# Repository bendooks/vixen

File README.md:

Reverse engineering a VIC-20 RAM expansion
==========================================

This is a project to reverse engineer a Commodore VIC-20 memory expansion
from the old 8-bit computer days. This repository has several versions of
the board, a talk describing the process and related documentation.

The [talk](./talk/) directory contains all the relevant presentation files
and the [pcb](./pcb) directory has various PCB design projects (currently
mostly in Eagle 7).

There are some [pictures](https://photos.app.goo.gl/yPw7znJ7fA79bZMN6) of
both the original boards and my rebuilds.

Links
-----

- FOSDEM 2020 [talk](https://archive.fosdem.org/2020/schedule/event/retro_reverse_engineering_vic_20_cartridge/)
- Computing history [page](http://www.computinghistory.org.uk/det/32521/Vixen-Switchable-16K-RAM/)
- Retro-computing [page](https://www.retrocomputers.online/product/vixen-switchable-16k-ram/) includes [manual](https://www.retrocomputers.online/wp-content/uploads/2020/11/Vixen16kRAM.pdf)
- Commodore info [page](https://www.commodore-info.com/cartridge/item/vixen_16k/en/desktop)
- Nightfall crea [page](https://www.nightfallcrew.com/18/05/2010/vixen-switchable-16k-ram-for-commodore-vic-20/) includes detailed pictures.

License
-------

All work is under CC-BY-SA v4 unless otherwise stated.

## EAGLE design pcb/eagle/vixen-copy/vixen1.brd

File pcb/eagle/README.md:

Eagle PCB files
===============

These are the PCB file projects for the re-build of the original [vixen-copy](./vixen-copy/) and a new variant which is modified to support 64KiB-ish memory expansion [vixen-copy-64k](./vixen-copy-64ki)

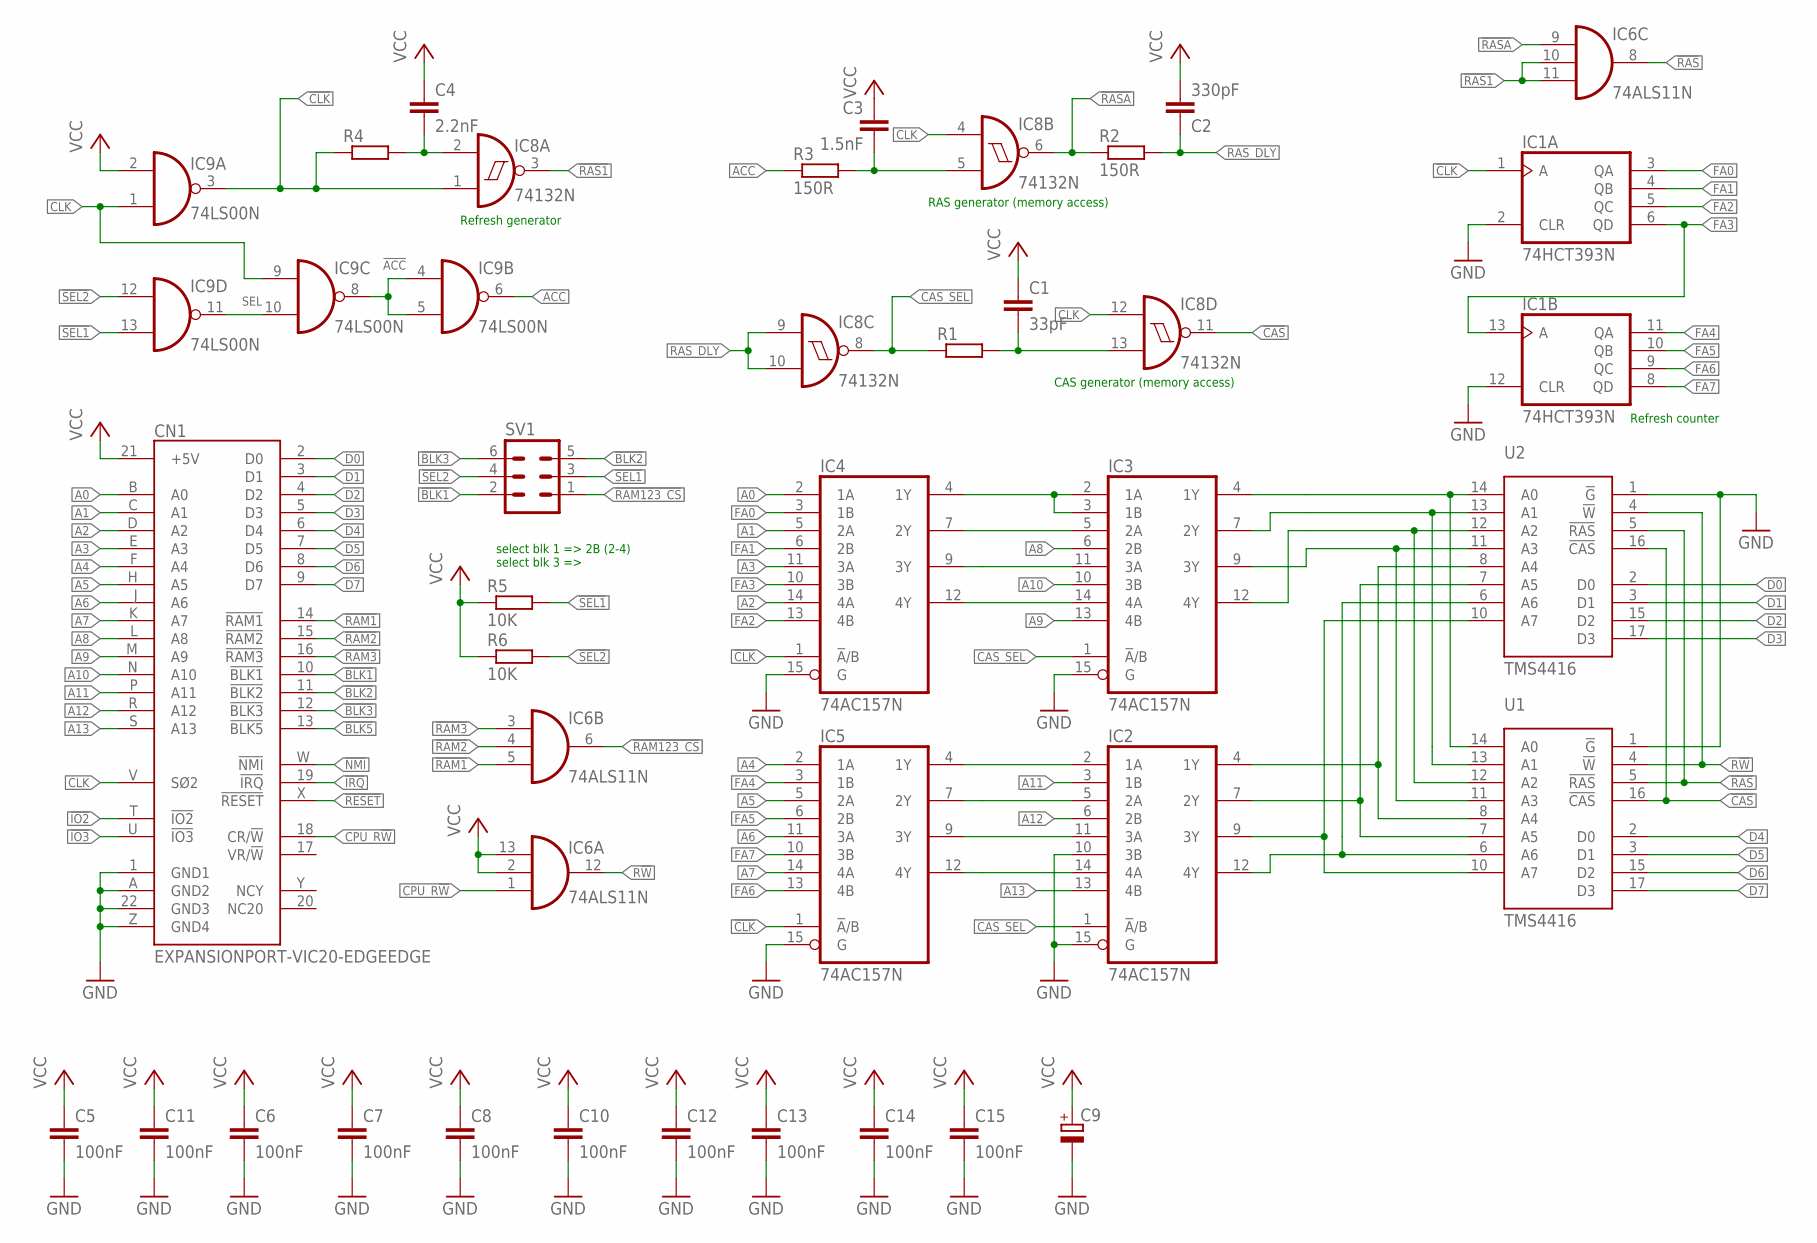
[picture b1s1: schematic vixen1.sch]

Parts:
C1: 33pF; C025-025X050
C2: 330pF; C025-025X050
C3: 1.5nF; C025-025X050
C4: 2.2nF; C025-025X050
C5, C6, C7, C8, C10, C11, C12, C13, C14, C15: 100nF; C025-025X050
C9: CPOL-EUE15-5AXIAL; E15-5
CN1: EXPANSIONPORT-VIC20-EDGEEDGE; UPS44EDGE
IC1: 74HCT393N; DIL14
IC2, IC3, IC4, IC5: 74AC157N; DIL16
IC6: 74ALS11N; DIL14
IC8: 74132N; DIL14
IC9: 74LS00N; DIL14
R1, R4: R-EU_0204/7; 0204/7
R2, R3: 150R; 0204/7
R5, R6: 10K; 0204/7
SV1: MA03-2
U1, U2: TMS4416; DIL18

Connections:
!ACC: IC9.4 (I0), IC9.5 (I1), IC9.8 (O)
!BLK1: CN1.10 (!BLK1), SV1.2
!BLK2: CN1.11 (!BLK2), SV1.5
!BLK3: CN1.12 (!BLK3), SV1.6
!BLK5: CN1.13 (!BLK5)
!CAS: IC8.11 (O), U1.16 (!CAS), U2.16 (!CAS)
!CLK: IC1.1 (A), IC4.1 (!A!/B), IC5.1 (!A!/B), IC8.1 (I0), IC9.3 (O), R4.1
!IO2: CN1.T (!IO2)
!IO3: CN1.U (!IO3)
!IRQ: CN1.19 (!IRQ)
!NMI: CN1.W (!NMI)
!RAM1: CN1.14 (!RAM1), IC6.5 (I2)
!RAM2: CN1.15 (!RAM2), IC6.4 (I1)
!RAM3: CN1.16 (!RAM3), IC6.3 (I0)
!RAM123_CS: IC6.6 (O), SV1.1
!RAS: IC6.8 (O), U1.5 (!RAS), U2.5 (!RAS)
!RAS1: IC6.10 (I1), IC6.11 (I2), IC8.3 (O)
!RASA: IC6.9 (I0), IC8.6 (O), R2.1
!RESET: CN1.X (!RESET)
!SEL1: IC9.13 (I1), R5.2, SV1.3
!SEL2: IC9.12 (I0), R6.2, SV1.4
A0: CN1.B (A0), IC4.2 (1A)
A1: CN1.C (A1), IC4.5 (2A)
A2: CN1.D (A2), IC4.14 (4A)
A3: CN1.E (A3), IC4.11 (3A)
A4: CN1.F (A4), IC5.2 (1A)
A5: CN1.H (A5), IC5.5 (2A)
A6: CN1.J (A6), IC5.11 (3A)
A7: CN1.K (A7), IC5.14 (4A)
A8: CN1.L (A8), IC3.6 (2B)
A9: CN1.M (A9), IC3.13 (4B)
A10: CN1.N (A10), IC3.10 (3B)
A11: CN1.P (A11), IC2.3 (1B)
A12: CN1.R (A12), IC2.6 (2B)
A13: CN1.S (A13), IC2.13 (4B)
ACC: IC9.6 (O), R3.1
CAS_RC: C1.2, IC8.13 (I1), R1.2
CAS_RC1: C4.2, IC8.2 (I1), R4.2
CAS_SEL: IC2.1 (!A!/B), IC3.1 (!A!/B), IC8.8 (O), R1.1
CLK: CN1.V (SØ2), IC8.4 (I0), IC8.12 (I0), IC9.1 (I0), IC9.9 (I0)
CPU_R!W: CN1.18 (CR/!W), IC6.1 (I0)
D0: CN1.2 (D0), U2.2 (D0)
D1: CN1.3 (D1), U2.3 (D1)
D2: CN1.4 (D2), U2.15 (D2)
D3: CN1.5 (D3), U2.17 (D3)
D4: CN1.6 (D4), U1.2 (D0)
D5: CN1.7 (D5), U1.3 (D1)
D6: CN1.8 (D6), U1.15 (D2)
D7: CN1.9 (D7), U1.17 (D3)
FA0: IC1.3 (QA), IC4.3 (1B)
FA1: IC1.4 (QB), IC4.6 (2B)
FA2: IC1.5 (QC), IC4.13 (4B)
FA3: IC1.6 (QD), IC1.13 (A), IC4.10 (3B)
FA4: IC1.11 (QA), IC5.3 (1B)
FA5: IC1.10 (QB), IC5.6 (2B)
FA6: IC1.9 (QC), IC5.13 (4B)
FA7: IC1.8 (QD), IC5.10 (3B)
GND: C5.2, C6.2, C7.2, C8.2, C9.-, C10.2, C11.2, C12.2, C13.2, C14.2, C15.2, CN1.1 (GND1), CN1.22 (GND3), CN1.A (GND2), CN1.Z (GND4), IC1.2 (CLR), IC1.7 (GND), IC1.12 (CLR), IC2.8 (GND), IC2.10 (3B), IC2.15 (G), IC3.8 (GND), IC3.15 (G), IC4.8 (GND), IC4.15 (G), IC5.8 (GND), IC5.15 (G), IC6.7 (GND), IC8.7 (GND), IC9.7 (GND), U1.1 (!G), U1.18 (GND), U2.1 (!G), U2.18 (GND)
R!W: IC6.12 (O), U1.4 (!W), U2.4 (!W)
RA0: IC3.4 (1Y), U1.14 (A0), U2.14 (A0)
RA1: IC3.7 (2Y), U1.13 (A1), U2.13 (A1)
RA2: IC3.12 (4Y), U1.12 (A2), U2.12 (A2)
RA3: IC3.9 (3Y), U1.11 (A3), U2.11 (A3)
RA4: IC2.4 (1Y), U1.8 (A4), U2.8 (A4)
RA5: IC2.7 (2Y), U1.7 (A5), U2.7 (A5)
RA6: IC2.12 (4Y), U1.6 (A6), U2.6 (A6)
RA7: IC2.9 (3Y), U1.10 (A7), U2.10 (A7)
RAS_DLY: C2.1, IC8.9 (I0), IC8.10 (I1), R2.2
RAS_RC1: C3.2, IC8.5 (I1), R3.2
ROW0: IC3.2 (1A), IC3.3 (1B), IC4.4 (1Y)
ROW1: IC3.5 (2A), IC4.7 (2Y)
ROW2: IC3.14 (4A), IC4.12 (4Y)
ROW3: IC3.11 (3A), IC4.9 (3Y)
ROW4: IC2.2 (1A), IC5.4 (1Y)
ROW5: IC2.5 (2A), IC5.7 (2Y)
ROW6: IC2.14 (4A), IC5.12 (4Y)
ROW7: IC2.11 (3A), IC5.9 (3Y)
SEL: IC9.10 (I1), IC9.11 (O)
VCC: C1.1, C2.2, C3.1, C4.1, C5.1, C6.1, C7.1, C8.1, C9.+, C10.1, C11.1, C12.1, C13.1, C14.1, C15.1, CN1.21 (+5V), IC1.14 (VCC), IC2.16 (VCC), IC3.16 (VCC), IC4.16 (VCC), IC5.16 (VCC), IC6.2 (I1), IC6.13 (I2), IC6.14 (VCC), IC8.14 (VCC), IC9.2 (I1), IC9.14 (VCC), R5.1, R6.1, U1.9 (VCC), U2.9 (VCC)

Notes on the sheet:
select blk 1 => 2B (2-4) select blk 3 =>
Refresh generator
RAS generator (memory access)
CAS generator (memory access)
Refresh counter

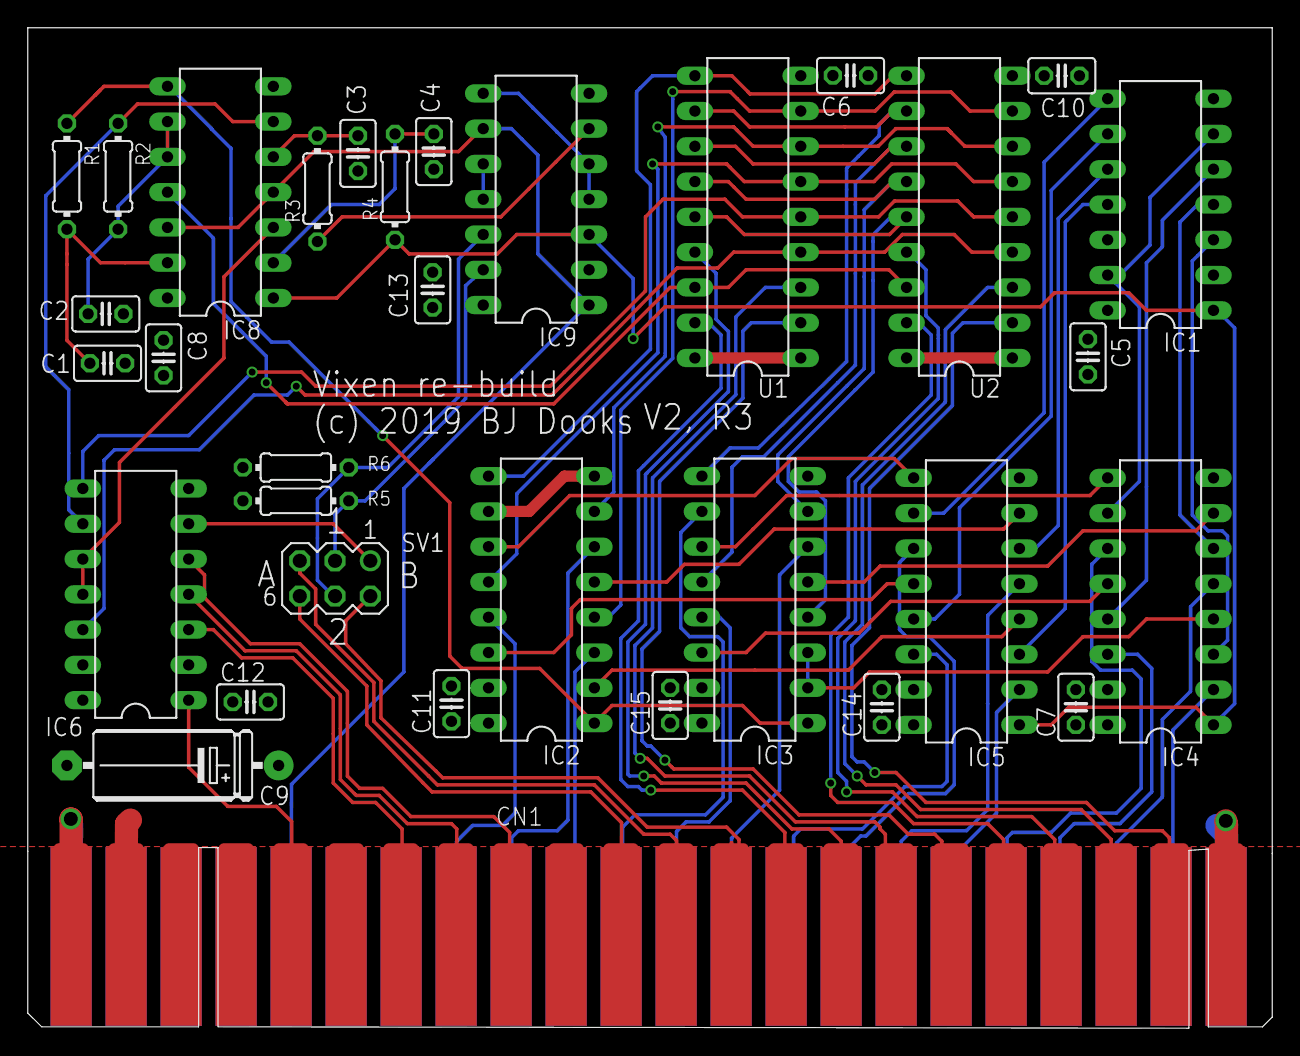
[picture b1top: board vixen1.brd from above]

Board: 2 copper layers, 89.6 x 72.0 mm, 33 parts (0 on the bottom side), 73 nets.

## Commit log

2020-01-26 Initialise with basic README.md
2020-01-26 Import eagle files from building real board
2020-01-26 ignore eagle backup files
2020-01-26 PCB release 1 manufacutring files
2020-01-30 initial readme for talk
2020-01-30 DRAM access state machine
2020-01-30 Simpler DRAM state machine
2020-01-30 Updated README file
2020-01-30 simple .gitignore for project
2020-01-30 Add initial state machine diagrams
2020-01-31 Add CC-BY-SA as license
2020-01-31 talk: add circuitjs reference
2020-01-31 talk: this isn't actually a javascript file
2020-01-31 Initial libreoffice presentation
2020-01-31 add datasheets
2020-01-31 talk: update libreoffice with new speakers notes
2020-02-01 talk: update copyright and notes for FOSDEM 2020
2021-04-19 add BLK5 to netlist
2021-04-19 fix pcb back version text to v2,r1
2021-04-19 v2r1 of the pcb
2021-04-22 Mark this release as broken
2021-04-22 added introduction section to top level readme
2021-04-22 initial work on 64KiB(ish) version of Vixen
2021-04-22 Add README file for Eagle directory
2021-04-22 Fix t-stop and v-stop layers to avoid soldermask on edge connector and incremen version
2021-04-22 Add schematic printout to avoid having to load eagle
2021-04-22 Add PDF version of slides
2021-04-22 updated 64k version schematic to fit in frame
2021-04-22 add initial notes on 64K version
2021-04-22 add schematic pdf, rename project files to vixen-64k.{sch,brd}
2021-04-28 add some useful links
2021-04-28 add some picture album
2021-05-06 minor soldermask updates, remove silkscreen out of board area
2021-05-06 vixen-64k: silkscreen updates and minor routing
2021-05-06 vixen-64k print final schematic
2021-05-06 vixen-64k: release1 data
2021-05-06 vixen: minor pcb updates for v2,r3

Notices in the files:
pcb/eagle/vixen-copy/vixen1.brd:
(c) 2019 BJ Dooks
